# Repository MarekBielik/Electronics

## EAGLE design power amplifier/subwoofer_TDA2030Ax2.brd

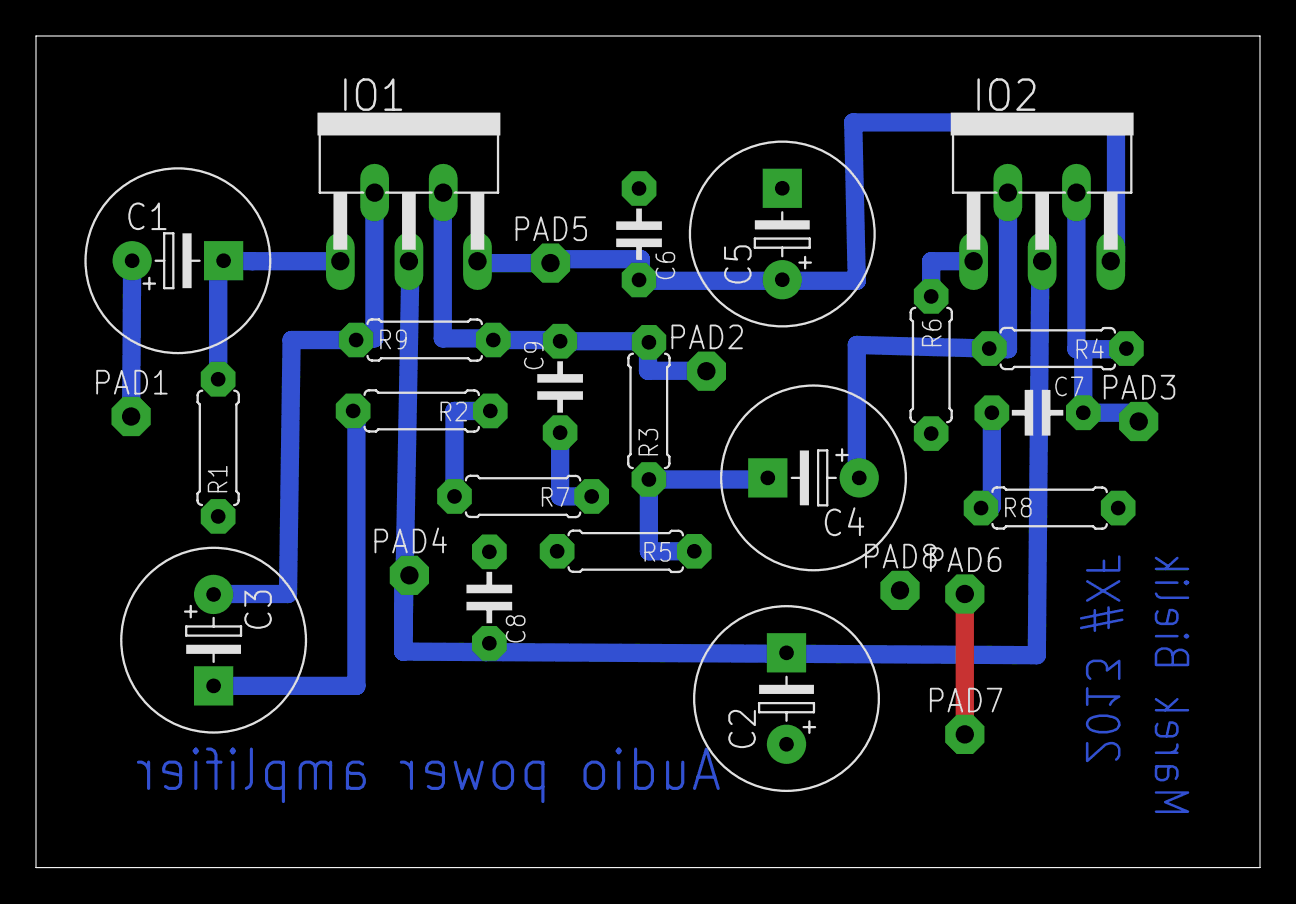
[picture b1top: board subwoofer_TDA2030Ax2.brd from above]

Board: 2 copper layers, 68.0 x 46.2 mm, 28 parts (0 on the bottom side), 14 nets.

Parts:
C1, C2, C3, C4, C5: C-EL_5
C6, C7, C8, C9: C-5
IO1, IO2: TDA2030; PENTAWAT
PAD1, PAD2, PAD3, PAD4, PAD5, PAD6, PAD7, PAD8: PAD_1
R1, R2, R3, R4, R5, R6, R7, R8, R9: R-7,5

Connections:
0V: C2.C+, C5.C-, C6.1, C8.1, PAD6.1, PAD7.1, PAD8.1, R1.1, R2.1, R5.2, R6.2, R7.2, R8.2
unnamed: C1.C+, PAD1.1
unnamed: C1.C-, IO1.1, R1.2
unnamed: C9.1, R7.1
unnamed: C3.C+, IO1.2, R9.1
unnamed: C3.C-, R2.2
unnamed: C4.C-, R3.1, R5.1
unnamed: C7.1, R8.1
unnamed: C4.C+, IO2.2, R4.2
unnamed: C9.2, IO1.4, PAD2.1, R3.2, R9.2
unnamed: C7.2, IO2.4, PAD3.1, R4.1
unnamed: C2.C-, C8.2, IO1.3, IO2.3, PAD4.1
unnamed: IO2.1, R6.1
unnamed: C5.C+, C6.2, IO1.5, IO2.5, PAD5.1

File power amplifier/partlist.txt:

Partlist

Exported from subwoofer_TDA2030Ax2.sch at 11. 8. 2013 14:22:31

EAGLE Version 6.0.0 Copyright (c) 1988-2011 CadSoft

Assembly variant: 

Part     Value          Device           Package  Library  Sheet

C1       2,2uF          C-ELEKTROLYT_3,5 C-EL_3,5 #PaJa_30 1
C2       100uF          C-ELEKTROLYT_3,5 C-EL_3,5 #PaJa_30 1
C3       22uF           C-ELEKTROLYT_3,5 C-EL_3,5 #PaJa_30 1
C4       22uF           C-ELEKTROLYT_3,5 C-EL_3,5 #PaJa_30 1
C5       100uF          C-ELEKTROLYT_3,5 C-EL_3,5 #PaJa_30 1
C6       100nF          C-KERAMIK_5      C-5      #PaJa_30 1
C7       0,22uF         C-KERAMIK_5      C-5      #PaJa_30 1
C8       100nF          C-KERAMIK_5      C-5      #PaJa_30 1
C9       0,22uF         C-KERAMIK_5      C-5      #PaJa_30 1
IO1      TDA2030        TDA2030          PENTAWAT #PaJa_30 1
IO2      TDA2030        TDA2030          PENTAWAT #PaJa_30 1
PAD1     PAD_1          PAD_1            PAD_1    #PaJa_30 1
PAD2     PAD_1          PAD_1            PAD_1    #PaJa_30 1
PAD3     PAD_1          PAD_1            PAD_1    #PaJa_30 1
PAD4     PAD_1          PAD_1            PAD_1    #PaJa_30 1
PAD5     PAD_1          PAD_1            PAD_1    #PaJa_30 1
PAD6     PAD_1          PAD_1            PAD_1    #PaJa_30 1
R1       22k            R_7,5            R-7,5    #PaJa_30 1
R2       680R           R_7,5            R-7,5    #PaJa_30 1
R3       22k            R_7,5            R-7,5    #PaJa_30 1
R4       22k            R_7,5            R-7,5    #PaJa_30 1
R5       680R           R_7,5            R-7,5    #PaJa_30 1
R6       22k            R_7,5            R-7,5    #PaJa_30 1
R7       1R             R_7,5            R-7,5    #PaJa_30 1
R8       1R             R_7,5            R-7,5    #PaJa_30 1
R9       22k            R_7,5            R-7,5    #PaJa_30 1

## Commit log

2016-01-12 wx receiver and power amplifier added

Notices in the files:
parts and their libraries:
Copyright (C) PaJa 2001-2011
